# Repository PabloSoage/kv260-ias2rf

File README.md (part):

# KV260-IAS2RF: an RF front-end carrier for the AMD Kria KV260

**Status (20 November 2026, Rev08.1): schematic and layout complete, on 8 layers. The board is fully routed, with zero
DRC errors and zero schematic-parity problems. It has not been fabricated, and no hardware has
been validated.** The hardware, dual-FPGA Vivado gateware, Enclosure v2 cooling, and full-system co-simulation are complete ([Status](#status)).

> **Current `main` Hardware & Gateware Baseline:** **8-layer `JLC08161H-2116C`** RF front-end adapter PCB with dedicated-pin **1000BASE-T Ethernet (`U1201 RTL8211FSI`) + dual-lane `IAS1` (`~2.94 Gb/s` aggregate)**, failover in the dual-FPGA Vivado 2026.1 gateware ([docs/FPGA_GATEWARE.md](docs/FPGA_GATEWARE.md)), `5 V` header `J1002` for filtered Enclosure v2 active cooling ([ENCLOSURE.md](docs/ENCLOSURE.md)), and `0` KiCad DRC / parity errors. Historical design evolution from initial drafts is archived in [docs/history/README.md](docs/history/README.md) and tagged `rev01` to `rev08.1`.

**Explore it in 3-D:** [pablosoage.github.io/kv260-ias2rf](https://pablosoage.github.io/kv260-ias2rf/). Turn the board, the KV260 and the enclosure, open the case, hover a part to see what it is and what it does, and look at the board layer by layer.

An adapter board for the **AMD Kria KV260 Vision AI Starter Kit**. It plugs into the KV260's IAS1
camera connector and carries the converters, a common clock and a front-end FPGA. It serves two
signal chains:

- **Software-defined radio**: HF to 30 MHz directly; FM, airband, VHF/UHF amateur bands, PMR446 and ADS-B
  through the on-board VHF/UHF front end on its own SMA, 30 MHz to 3 GHz ([RX_VU_SPEC](docs/RX_VU_SPEC.md)).
  Receive, and transmit on the bands a licence covers.
- **Radar at 10.5 GHz**: the IF of the X-band chain from the open
  [AERIS-10 / PLFM_RADAR](https://github.com/NawfalMotii79/PLFM_RADAR) project, with ADAR1000
  beamforming. The 10.5 GHz chain itself is reused from AERIS-10, not redesigned here. The board
  is sized for 8 ADAR1000s (32 channels), so it covers both the Nexus variant (4 chips) and the
  Extended one (8 chips).

> ### The finding that shapes the whole project
>
> The **IAS0 (J7) connector on the KV260 does not reach the programmable logic**: its MIPI lanes
> run into an AP1302 ISP soldered on the carrier card. Only **IAS1 (J8)** is wired straight to
> the SOM. On top of that, **the KV260 has no 40-pin Raspberry Pi header** (J9 is a 15-pin
> camera connector), and **the GTH transceivers are not exposed**.
>
> The real I/O budget between a KV260 and an external board is **8 differential pairs and about
> 14 single-ended signals**. That is why the board has its own FPGA. The evidence and sources are
> in [docs/BLOCKERS_AND_RISKS.md](docs/BLOCKERS_AND_RISKS.md).

---

## The board at a glance

| | |
|---|---|
| Size | 119 × 132 mm, 140 × 132 with the RJ45's tab. It mounts on the KV260's IAS connectors and corner holes and overhangs to one side ([INTERFACE_SPEC §5.3](docs/INTERFACE_SPEC.md)) |
| Stackup | 8 layers, JLCPCB `JLC08161H-2116C`: `L1 SIG – L2 GND – L3 SIG – L4 PWR (split) – L5 GND – L6 SIG – L7 GND – L8 SIG` ([LAYOUT §3](docs/LAYOUT.md)) |
| Parts | 785 fitted, the same count as the BOM and the placement file: 620 on the top face and 165 on the bottom (the Hirose connectors, the LVDS terminations and VCCINT caps under the FPGA, the switches' bias parts, the input protection) |
| Front-end FPGA | Xilinx XC7A50T-2FTG256I (the same part as AERIS-10) with a 128 Mb QSPI flash, plus JTAG |
| Radar ADC | AD9484, 8 bit: 400 MSPS with the 400 MHz master clock (radar), 500 MSPS with the 500 MHz one (the D2 path), driven by two cascaded AD8352s |
| SDR ADC | AD9253, 14 bit, two channels at 62.5 MSPS (one LVDS lane each) |
| Radar DAC | AD9708, with reconstruction filter and balun |
| SDR DAC | AD9767, dual 14 bit, two output chains |
| Clock | Si549 programmable XO (400 or 500 MHz, GPS-disciplinable) into an ADCLK948 LVPECL fan-out |
| RF routing | Four M3SWA2-34DR+ SPDT switches and ten edge SMAs, plus two clock SMAs and the VHF/UHF antenna SMA `J961` on the back wall: thirteen in all. The HF ports J951 (receive, through an on-board 30 MHz 7th-order elliptic anti-alias filter) and J952 (transmit) have no switch in their path ([SIGNAL_INTEGRITY §9.9](docs/SIGNAL_INTEGRITY.md)) |
| Link to the Kria | IAS1 (Hirose BM20B), five LVDS pairs at up to 1 Gb/s each, AC-coupled; the Pmod J2 for control |
| Ethernet | Gigabit RJ45 through an RTL8211FSI SGMII PHY on its own FPGA pins, so it runs alongside IAS1 ([CONTROL_SPEC §8](docs/CONTROL_SPEC.md)) |
| To AERIS-10 | 2×20 IDC ribbon for eight ADAR1000s |
| Power | 12 V single power entry (`J1001` via `L1004` to adapter + `U1010`/`J1004` 3.0 A output to KV260 `J12`); buck and LDO tree for 5 V, 3.3 V, 2.5 V, 1.8 V and 1.0 V, plus -3.3 V for the switches ([POWER_SPEC §1.4](docs/POWER_SPEC.md), [BOARD_MANUAL §6](docs/BOARD_MANUAL.md#6-powering-the-kv260-together-with-the-board)). In a vehicle, the [PSU board](docs/PSU_SPEC.md) feeds both boards from the battery |

```mermaid
flowchart LR
  KV260["Kria KV260<br/>(K26 SOM)"] <-- "IAS1: 5 LVDS pairs<br/>Pmod: control" --> FPGA["XC7A50T<br/>front-end FPGA"]
  FPGA <-- LVDS --> ADCR["AD9484<br/>radar ADC"]
  FPGA <-- LVDS --> ADCS["AD9253<br/>SDR ADC"]
  FPGA --> DACR["AD9708<br/>radar DAC"]
  FPGA --> DACS["AD9767<br/>SDR DAC"]
  CLK["Si549 + ADCLK948<br/>clock"] --> ADCR & ADCS & DACR & DACS & FPGA
  ADCR & ADCS & DACR & DACS <--> RF["RF switches<br/>10 SMAs"]
  FPGA <-- "IDC ribbon" --> AERIS["AERIS-10<br/>8 × ADAR1000"]
  RF <--> AERIS
```

| Top | Bottom |
|---|---|
|  |  |

The renders come from KiCad. The shield frames' walls show only their pads; the debug USB-C `J1501` has a model
drawn from its maker's drawing, since no library has one ([3D_MODELS](docs/3D_MODELS.md)).

---

<!-- board-manual:start -->
## Board manual

Every connector, LED, switch and chip, numbered as in the drawing; the bottom side, the switches, the chips, troubleshooting and typical uses are in [docs/BOARD_MANUAL.md](docs/BOARD_MANUAL.md). Generated with the tables from the board file by `_work/manual/board_manual.py`.

| No. | Ref | Side | Name | What it is for |
|---|---|---|---|---|
| 1 | `J101` | bottom | BM20B(0.8)-34DP | IAS1 to the KV260 (its `J8`), underneath: five LVDS pairs at up to 1 Gb/s each (three data lanes, two clocks), the housekeeping I2C (temperature sensor, ID EEPROM) and the FPGA's interrupt. The board's only data link to the Kria |
| 2 | `J102` | bottom | BM20B(0.8)-34DP | IAS0 to the KV260 (its `J7`), underneath. Every pin is passed through to `J103`; the board uses none |
| 3 | `J103` | top | BM20B(0.8)-34DS-0.4V(51) | IAS0 pass-through receptacle on the tongue's top face, pin for pin with `J102`: an IAS camera module plugs in here as it would on the carrier |
| 4 | `J401` | top | CLK_REF_IN | Reference clock input (SMA) to the ADCLK948, 0.4-3.4 V p-p differential range, 50 ohm on chip. Leave open to run from the on-board Si549 |
| 5 | `J402` | top | CLK_OUT | Clock output (SMA), ADCLK948 Q3, LVPECL: to share the master clock with an instrument |
| 6 | `J911` | top | SDR_RX_A | SDR receive A (SMA): through SW1's default throw to the AD9253 channel A. Full scale about -2.4 dBm; DC-blocked |
| 7 | `J912` | top | AERIS_IF_A | Radar IF into the 14-bit AD9253 (SMA), through SW1's second throw |
| 8 | `J921` | top | AERIS_IF | Radar IF from AERIS-10 (SMA): through SW2's default throw to the AD9484 (400 or 500 MSPS with the master clock). Full scale about -17.6 dBm |
| 9 | `J922` | top | SDR_RX_WB | Wideband SDR receive (SMA), SW2's second throw. Not connected as built: `C926` is not fitted and the VHF/UHF front end takes the throw (`C927`); swap the two 0402s to use this port |
| 10 | `J931` | top | SDR_TX_A | SDR transmit A (SMA): AD9767 DAC1 through SW3's default throw, 10 mA full scale |
| 11 | `J932` | top | AERIS_TX_A | Radar chirp from the 14-bit AD9767 DAC1 (SMA), SW3's second throw |
| 12 | `J941` | top | AERIS_TX | Radar chirp to AERIS-10 (SMA): the AD9708 through SW4's default throw, 20 mA full scale into a 2:1 balun |
| 13 | `J942` | top | SDR_TX_WB | Wideband SDR transmit from the AD9708 (SMA), SW4's second throw |
| 14 | `J951` | top | SDR_RX_C | HF receive (SMA), no switch: a 30 MHz 7th-order elliptic low-pass, then the AD9253 channel B. Full scale about -3.0 dBm. The default HF input |
| 15 | `J952` | top | SDR_TX_C | HF transmit (SMA), no switch: AD9767 DAC2. The default HF output |
| 16 | `J961` | top | VU_ANT | VHF/UHF antenna (SMA, back wall): the Rev08 front end, direct 30-170 MHz and converted from 300 MHz to 3 GHz (170-300 MHz not covered: the converter's 300 MHz high-pass, AUDIT_Rev08 R1), into the AD9484 through SW2. Bias tee for an active antenna (off at power-up, 5 V or 3.3 V by `JP1301`, 125 mA limit; prefer 3.3 V where the antenna accepts it). Full scale -52 dBm at maximum gain, up to about +2 dBm with the attenuator and the LNA bypassed. No limiter: keep it away from a transmitter on the same vehicle (+25 dBm destroys the LNA) |
| 17 | `J1001` | top | 12V IN | 12 V input, barrel jack (CUI PJ-102AH, 5 A). Single power entry for both boards (`L1004` on both lines): feeds the adapter (11.7 W typical, 13.4 W / 1.12 A worst; `F1001` 2 A PTC, 18.3 V OVP) and the KV260 via `U1010`/`J1004` (3.0 A / 3.19 A max limit; 1.89 A typical, 4.12 A rated, 4.31 A worst combined). See POWER_SPEC section 1.4 and section 6 |
| 18 | `J1002` | top | FAN 5V | Enclosure fan, JST PH 2-pin: pin 1 +5 V (0.5 A PTC `F1002`), pin 2 GND |
| 19 | `J1004` | top | B2PS-VH | 12 V output to the KV260's `J12` (JST VH 2-pin right-angle, 10 A: pin 1 `+12V_KV`, pin 2 `GND`): protected by `U1010` (8.0 V UVLO, 14.4 V OVP, 3.0 A limit via `R1043` 6.04 kohm, -60 V reverse); see section 6 |
| 20 | `J1101` | top | JTAG 2x7 2mm | Xilinx JTAG for the XC7A50T and its flash (Platform Cable or any 2 mm 14-pin JTAG adapter) |
| 21 | `J1102` | top | Pmod | Pmod from the KV260's `J2` (cable): SPI to the FPGA's register file, beam strobe, PPS and the debug UART. Pin by pin below |
| 22 | `J1103` | top | AERIS ADAR | AERIS-10 beam-steering ribbon (2x20 IDC): the ADAR1000 SPI and its control lines |
| 23 | `J1201` | top | HR911130C | Gigabit Ethernet (RJ45, magnetics and LEDs inside), from the RTL8211FS over SGMII to the FPGA: the board standalone |
| 24 | `J1501` | top | TYPE-C-31-E-17 | Debug USB-C (vertical, on the tongue): the FPGA's console through a CH340X, 115,200 baud 8N1, powered from the cable. Lid off |
| 25 | `J1502` | top | FPC-1.0FX-15PWCR-H20 | GPS PPS and the vehicle CAN to the KV260's `J9` (Raspberry Pi camera connector) by a 100 mm 15-way 1 mm FFC, either cable type: the pulse reaches `J9` pin 12, a PL pin (`kria_pps`); CAN TX leaves on `J9` pin 6 and RX comes back on pin 8 (PS `CAN1`, R5F core 1) |
| 26 | `J1503` | top | BM06B-SRSS-TB | GPS receiver and vehicle CAN, JST-SH 6-pin, vertical, the plug from above: 1 GND, 2 CANL, 3 CANH, 4 GND, 5 PPS in (3.3 V), 6 +3.3 V out (0.2 A PTC) (no termination: it taps the car's bus) |

| No. | LED | Meaning when lit |
|---|---|---|
| 30 | `D1501` CFG green | FPGA configured and the clock sequencer finished |
| 30 | `D1502` CLK yellow | Master clock mode: on 500 MHz, off 400 MHz |
| 30 | `D1503` LINK green | IAS1 link to the Kria trained |
| 30 | `D1504` ADCR red | The radar ADC (AD9484) clipped since the last read (sticky) |
| 30 | `D1505` ADCS red | The SDR ADC (AD9253) clipped since the last read (sticky) |
| 30 | `D1506` LO green | The RFFC5072 synthesiser is locked |
| 30 | `D1507` TX red | A DAC is driving an SMA |
| 30 | `D1508` ERR red | Any sticky error: CRC, FIFO overflow, I2C no-acknowledge, over-temperature |
| 30 | `D1509` HB blue | Heartbeat: flickers with every line the FPGA prints on the debug UART, once a second |
| 31 | `D1520` +12V green | +12V present (after the input protection) |
| 31 | `D1521` +5V0 green | +5V0 present |
| 31 | `D1522` +3V3_D green | +3V3_D present |
| 31 | `D1523` +1V8_D green | +1V8_D present (switched from +3V3_D by `Q1520`) |
| 31 | `D1524` +1V0 green | +1V0 (FPGA core) present (switched from +3V3_D by `Q1521`) |
| 32 | `D1101` green | DONE: the FPGA has loaded a bitstream |
<!-- board-manual:end -->

---

## Schematics and layout

The PDFs and the high-resolution files are not in the repository: they are assets of the [`rev08.1` release](https://github.com/PabloSoage/kv260-ias2rf/releases/tag/rev08.1) (each older tag has its own), and the books open in the [online reader](https://pablosoage.github.io/kv260-ias2rf/pdf.html?file=docs/KV260-IAS2RF_Documentation.pdf).

- **[Schematic, all 12 sheets including full wired overview (PDF)](https://github.com/PabloSoage/kv260-ias2rf/releases/download/rev08.1/KV260-IAS2RF_schematic.pdf)** · [High-res SVGs & 4K PNGs](https://github.com/PabloSoage/kv260-ias2rf/releases/download/rev08.1/KV260-IAS2RF_highres.zip) ([index](docs/img/highres/README.md#1-schematics-sch))
- **[Layout, all 8 copper layers + combined + transparent tracks (PDF)](https://github.com/PabloSoage/kv260-ias2rf/releases/download/rev08.1/KV260-IAS2RF_layout.pdf)** · [Per-layer SVGs & 4K PNGs](https://github.com/PabloSoage/kv260-ias2rf/releases/download/rev08.1/KV260-IAS2RF_highres.zip) ([index](docs/img/highres/README.md#2-8-layer-pcb-layout-layout))
- **[Complete Project Documentation Book (PDF)](https://github.com/PabloSoage/kv260-ias2rf/releases/download/rev08.1/KV260-IAS2RF_Documentation.pdf)**, and the same book lighter, with the normal renders instead of the 4K ones: [Lite PDF](https://github.com/PabloSoage/kv260-ias2rf/releases/download/rev08.1/KV260-IAS2RF_Documentation-Lite.pdf) (both reproducible locally via [`export_documentation.py`](export_documentation.py), `--lite` for the second)
- KiCad 10 sources: [`KV260-IAS2RF.kicad_pro`](KV260-IAS2RF.kicad_pro), the root
  schematic and [`sheets/`](sheets/) (twelve hierarchical sheets), the 8-layer board
  [`KV260-IAS2RF.kicad_pcb`](KV260-IAS2RF.kicad_pcb), and custom libraries in
  [`symbols/`](symbols/) and [`footprints/`](footprints/). Every title block carries the revision, Rev08.1; the original Allied Vision Altium project the board started from stays in `PCB/` under its own name ([docs/history/README.md](docs/history/README.md)).

| Sheet | Contents | Specification |
|---|---|---|
| [Full Circuit](docs/img/sch/ROOT.png) | Complete wired schematic overview & hierarchy (`FULL_CIRCUIT` + `ROOT`) | [ARCHITECTURE](ARCHITECTURE.md) |
| [IAS_LINK](docs/img/sch/IAS_LINK.png) | The Hirose connectors, AC coupling and terminations of the link | [IAS_LINK_SPEC](docs/IAS_LINK_SPEC.md) |
| [CLOCK](docs/img/sch/CLOCK.png) | Si549, reference select and LVPECL fan-out | [CLOCK_SPEC](docs/CLOCK_SPEC.md) |
| [ADC_RADAR](docs/img/sch/ADC_RADAR.png) | AD9484 and its two AD8352 drivers | [ADC_RADAR_SPEC](docs/ADC_RADAR_SPEC.md) |
| [ADC_SDR](docs/img/sch/ADC_SDR.png) | AD9253, two channels | [ADC_SDR_SPEC](docs/ADC_SDR_SPEC.md) |
| [DAC_RADAR](docs/img/sch/DAC_RADAR.png) | AD9708, filter and balun | [DAC_RADAR_SPEC](docs/DAC_RADAR_SPEC.md) |
| [DAC_SDR](docs/img/sch/DAC_SDR.png) | AD9767 in interleaved mode, two output chains | [DAC_SDR_SPEC](docs/DAC_SDR_SPEC.md) |
| [ROUTING](docs/img/sch/ROUTING.png) | Four RF switches and the SMAs | [ROUTING_SPEC](docs/ROUTING_SPEC.md) |
| [CONTROL](docs/img/sch/CONTROL.png) | The front-end FPGA: banks, configuration, Pmod, AERIS ribbon, housekeeping | [CONTROL_SPEC](docs/CONTROL_SPEC.md) |
| [POWER](docs/img/sch/POWER.png) | The power tree | [POWER_SPEC](docs/POWER_SPEC.md) |
| [RX_VU](docs/img/sch/RX_VU.png) | VHF/UHF front end (`J961`), LNA, preselectors, RFFC5072 and IF chain | [RX_VU_SPEC](docs/RX_VU_SPEC.md) |
| [STATUS](docs/img/sch/STATUS.png) | Status LEDs, TCA6416A expanders, debug USB-C UART, GPS PPS and vehicle CAN | [BOARD_MANUAL](docs/BOARD_MANUAL.md#3-leds) |
| [KVPWR](docs/img/sch/KVPWR.png) | KV260 single-entry power feed: `J1004`, `L1004` CMC, `U1010` 3.0 A eFuse | [POWER_SPEC](docs/POWER_SPEC.md#14-single-power-entry-and-the-kv260-output-rev08-19-nov) |

> *High-resolution vector PDF (`sch/FULL_CIRCUIT.pdf` in the [high-res archive](https://github.com/PabloSoage/kv260-ias2rf/releases/download/rev08.1/KV260-IAS2RF_highres.zip)) and 4K schematic PNGs are indexed in [docs/img/highres/README.md](docs/img/highres/README.md).*

---

## Status

| Check | Result |
|---|---|
| ERC | 0 errors; 7 warnings, all explained: configuration and XADC pins tied to power on purpose ([CONTROL_SPEC §5](docs/CONTROL_SPEC.md)) |
| DRC, zones refilled | **0 errors, 0 unrouted connections, 0 schematic-parity problems** on the 8-layer `JLC08161H-2116C` board (`local/kvpwr`, 785 BOM parts; checked by `make_fab.py`) |
| Signal and power integrity | Full-wave openEMS + ngspice verification ([SIGNAL_INTEGRITY.md](docs/SIGNAL_INTEGRITY.md)): SMA launch `S11 = -30.9 dB` at 1 GHz (`-13.7 dB` at 3 GHz) with ESD diode, LVDS eyes within `1–26 mV` of ideal except `LINK_RX_D0` (`-52 mV`), worst intra-pair skew `9 ps`, `VCCINT` impedance `41 / 63 mΩ` (`target 120 mΩ`), ESD protection on every SMA, Pmod and JTAG, GND via within `3 mm` of all `89` LVDS layer changes |
| Planes | L2, L5, and L7 carry solid ground; L4 carries split power islands (`_work/layout/planechk.py`) |
| Dual-FPGA gateware | Both designs place, route and meet timing in Vivado 2026.1; utilisation and slack in the [FPGA figures](#fpga-figures) table, generated from the Vivado reports. They pass the end-to-end XSim suite (`tb_system`, `S1..S6`) and the G-8 simulations ([FPGA_GATEWARE.md](docs/FPGA_GATEWARE.md)) |
| Final RF review (15 Nov) | Five limits found ([SIGNAL_INTEGRITY §9.8](docs/SIGNAL_INTEGRITY.md)) and addressed ([§9.9](docs/SIGNAL_INTEGRITY.md)): a 30 MHz 7th-order anti-alias filter on the HF input J951 (≥ 60 dB from 50 MHz); the switch-free J951/J952 as the default HF ports; DAC clocks from `CLK_FPGA` ÷ 4 without an MMCM (clock uncertainty `0.165 → 0.035 ns`); no transmit copper within 1.5 mm of any receive line; the enclosure's honest rating below. Still to measure on the first board: TX→RX isolation, the RF switches at 1–5 MHz, the filter above 700 MHz, switcher spurs |
| Rev08 front end and diagnostics (16–17 Nov) | VHF/UHF receive on `J961`, 30 MHz to 3 GHz: noise figure 2.0 dB and full scale −52 dBm at maximum gain in the direct VHF path, FM-reject ≥ 40 dB with real tolerances; `J961` launch `S11 ≤ −18.1 dB` to 1.1 GHz with its ESD diode and bias tee; no front-end copper within 1.5 mm of either ADC input or the clock tree ([REV08_PLAN §5.5, §11.7](docs/REV08_PLAN.md), [SIGNAL_INTEGRITY §9.10](docs/SIGNAL_INTEGRITY.md)). 14 status and rail LEDs, a USB-C debug console, the IAS0 camera pass-through, and the [board manual](docs/BOARD_MANUAL.md) |
| Rev08.1 power and the PSU board (19 Nov) | One supply and one ground for both boards (sheet `KVPWR`, [POWER_SPEC §1.4](docs/POWER_SPEC.md), [AUDIT_Rev08 §6](docs/AUDIT_Rev08.md)); the [PSU board](docs/PSU_SPEC.md) feeds both from the battery through ISO 16750-2 Load Dump A/B, jump start and cranking Levels I, II and IV; its audit, ERC 0 and DRC 0 / 0 ([PSU_SPEC §10](docs/PSU_SPEC.md)) |
| Mechanical fit | Registered on AMD's 3D model of the KV260: mounting holes land within `5 µm` ([INTERFACE_SPEC §5.3](docs/INTERFACE_SPEC.md)) |

**Design & verification highlights** ([docs/LAYOUT.md](docs/LAYOUT.md), [docs/SIGNAL_INTEGRITY.md](docs/SIGNAL_INTEGRITY.md)):

1. **Power & analog isolation.** Supply trunks widened (`865 mm` at `>= 0.5 mm`); `+1V8_A` trimmed to `1.85 V`; DAC1/DAC2 filters colocated under their baluns (`T801`/`T802`), dropping balun common mode by `9–21 dB` (DAC2) and `1–6 dB` (DAC1); `FB401` upgraded to a `2 A / <= 0.1 Ω` bead (`48 mV` drop max, `0.1–0.4 mVpp` ripple on the clock tree).
2. **Differential pairs & LVDS routing.** Nine of 19 data/link pairs plus `CLK_ADCS` and `CLK_FPGA` run coupled `100 Ω` end-to-end on L1/L3/L6; the remaining pairs use `50 Ω` legs matched to `<= 9 ps` worst-case intra-pair skew with on-pad `100 Ω` terminations.
3. **ADCR data to DCO skew (`-90 to +5 ps`).** `ADCR_DCO` legs are swapped cleanly at the Artix-7 BGA (`N14 = DCO_N`, `P14 = DCO_P`); `adc_capture.v` compensates with `ISERDESE2` inversion + per-bit `IDELAYE2` calibration.
4. **8-layer `JLC08161H-2116C` fabrication stack.** Controlled impedances verified against JLCPCB's solver ([FABRICATION.md](docs/FABRICATION.md)); 5 bare boards quoted at `$287.96` (`140 × 132 mm` with Ethernet tab).
5. **Kria IAS1 I/O standard.** `DIFF_SSTL12` with `RTT_48` on-die split termination (`~96 Ω` to `0.6 V`) and `RDRV_60_60` driver ([INTERFACE_SPEC §6.3](docs/INTERFACE_SPEC.md)); `2 Gb/s` uplink (`2` pairs) + `1 Gb/s` downlink (`1` pair), `1.25 Gb/s` per lane silicon headroom.
6. **3-D full-wave EM, RF cascade & thermal envelope.** openEMS 3-D sub-models cover L1–L6 vias (`S11 < -29 dB`), BGA escapes (`< -24 dB`), adjacent-pair NEXT (`1.9%`), and `J101` launch (`< -25 dB`). Receive cascades (`cascade.py`) give `NF = 26.8 dB` (radar) / `22 dB` (SDR). Enclosure v2 (`50 × 50 × 15 mm` filtered lid fan + `HS1`–`HS3` heatsinks) is rated for `56 °C` ambient with the stock KV260, whose commercial K26 is the limit (`Tj` `85 °C`), and `70 °C` with an industrial K26I SOM, unchanged by Rev08's front end and camera ([ENCLOSURE_V2_THERMAL.md §8](docs/ENCLOSURE_V2_THERMAL.md)).
7. **Dual-FPGA Vivado 2026.1 gateware & XSim verification.** Full RTL, constraints, Vivado post-route floorplans/schematics, and XSim end-to-end testbenches live in `fpga/` ([docs/FPGA_GATEWARE.md](docs/FPGA_GATEWARE.md)). *(Design evolution history is archived in [docs/history/README.md](docs/history/README.md).)*

**Estimated cost** ([docs/JLCPCB_QUOTE.md](docs/JLCPCB_QUOTE.md)): about **$2,443 for two assembled boards** and **$4,785 for five** (19 Nov, single power entry + RJ45 shield RC; parts + assembly + `JLC08161H-2116C` bare boards).

---

## Documentation

| Document | Contents |
|---|---|
| **[docs/BOARD_MANUAL.md](docs/BOARD_MANUAL.md)** | **Board manual.** Every connector, LED, switch, jumper, test point and chip, with drawings of both sides, the Pmod pin-out, troubleshooting by LED and typical uses |
| **[docs/PSU_SPEC.md](docs/PSU_SPEC.md)** | **PSU board.** The battery-to-both-boards supply (`psu/`): LTC4364 surge stopper and LM5177 buck-boost, its simulations (steady state, loop, ISO 7637-2 and 16750-2 events, thermal, conducted noise) and installation |
| [docs/PSU_ENCLOSURE.md](docs/PSU_ENCLOSURE.md) | The PSU board's printed enclosure: honeycomb tray and lid, coupled thermal model (vents or sealed, ASA or PETG-CF), CalculiX FEA and renders |
| **[docs/VEHICLE_PLATFORM.md](docs/VEHICLE_PLATFORM.md)** | **System view.** Complete vehicle platform: LiDAR, SDR, radar, OBD2 |
| [docs/FPGA_GATEWARE.md](docs/FPGA_GATEWARE.md) | **Dual-FPGA Gateware.** Artix-7 + Kria K26 RTL, Vivado 2026.1 utilization/timing/floorplans/schematics, CSR map, wideband SDR & AERIS-10 radar DSP, and XSim e2e simulation |
| [docs/HMI.md](docs/HMI.md) | **In-car HMI.** The ten touchscreen screens, a Slint application in Rust that runs on the KV260 (Linux KMS), a PC or a phone's browser, its data service and the PL's result streams behind it, and which job runs on the PL, the A53s, the R5F cores, the GPU and the VCU |
| [docs/INTEGRATIONS.md](docs/INTEGRATIONS.md) | **Possible integrations.** USB GPS, a 77 GHz radar over CAN, engine live data through opendash (measured against an emulated ECU), a 3D LiDAR, their behaviour in fog, and `kria_bev_grid`, a fusion occupancy grid for the PL |
| [KV260-IAS2RF_Documentation.pdf](https://github.com/PabloSoage/kv260-ias2rf/releases/download/rev08.1/KV260-IAS2RF_Documentation.pdf) (release asset) | **Unified Offline Book.** Every document of the project in one PDF, with the vector Vivado floorplans, the 14-page schematic (12 sheets), the 10-page 8-layer layout, the PSU board's schematic and 5-page 4-layer layout, 4K renders, and simulations (generated via [`export_documentation.py`](export_documentation.py)) |
| [docs/SHOPPING_LIST.md](docs/SHOPPING_LIST.md) | Parts and checklist per stage, with indicative costs |
| [ARCHITECTURE.md](ARCHITECTURE.md) | Master system architecture and BOM |
| [docs/BLOCKERS_AND_RISKS.md](docs/BLOCKERS_AND_RISKS.md) | Engineering blockers closed, with evidence and sources, plus open risks |
| [docs/INTERFACE_SPEC.md](docs/INTERFACE_SPEC.md) | Pin map for J8 and the Pmod, mechanical envelope, adapter registration on KV260 |
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
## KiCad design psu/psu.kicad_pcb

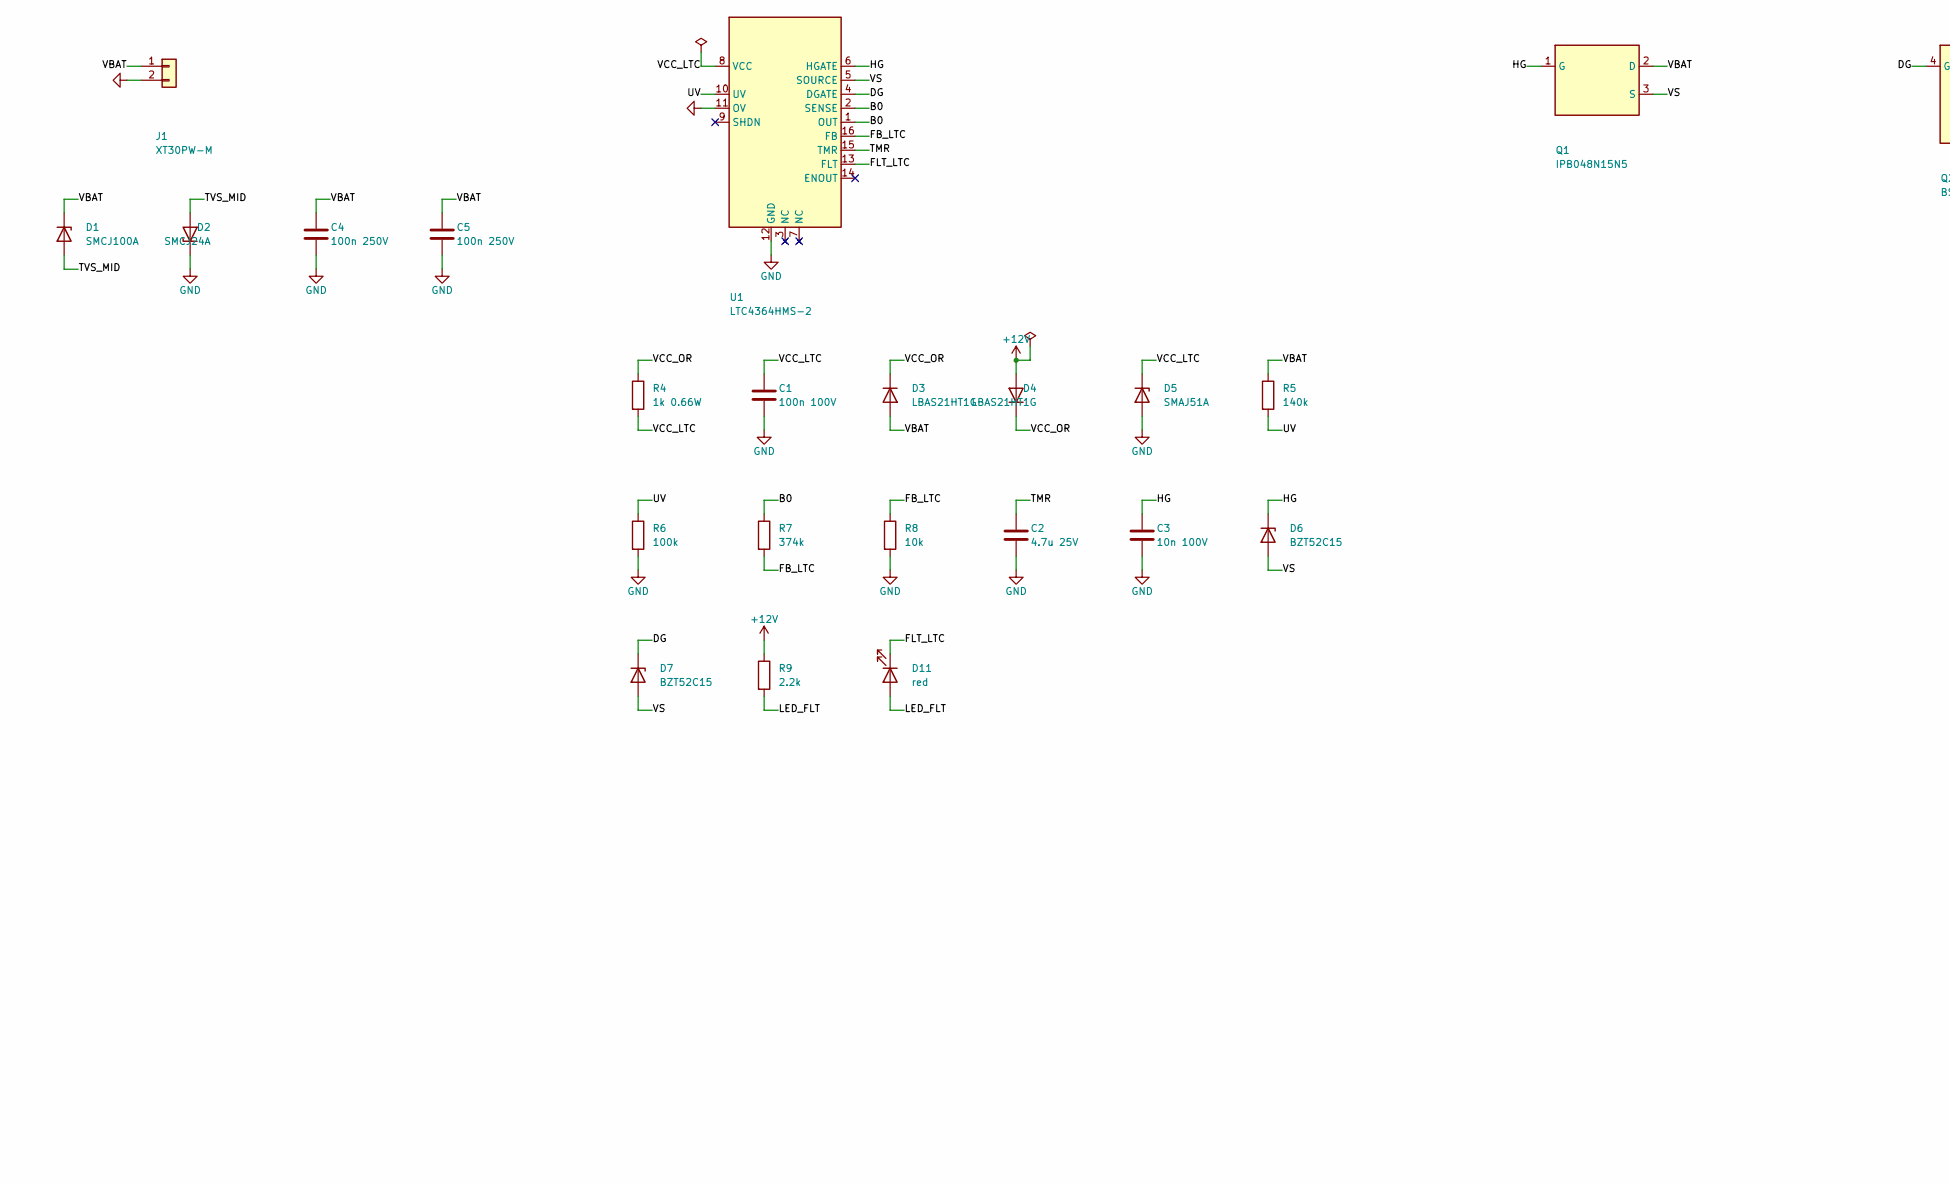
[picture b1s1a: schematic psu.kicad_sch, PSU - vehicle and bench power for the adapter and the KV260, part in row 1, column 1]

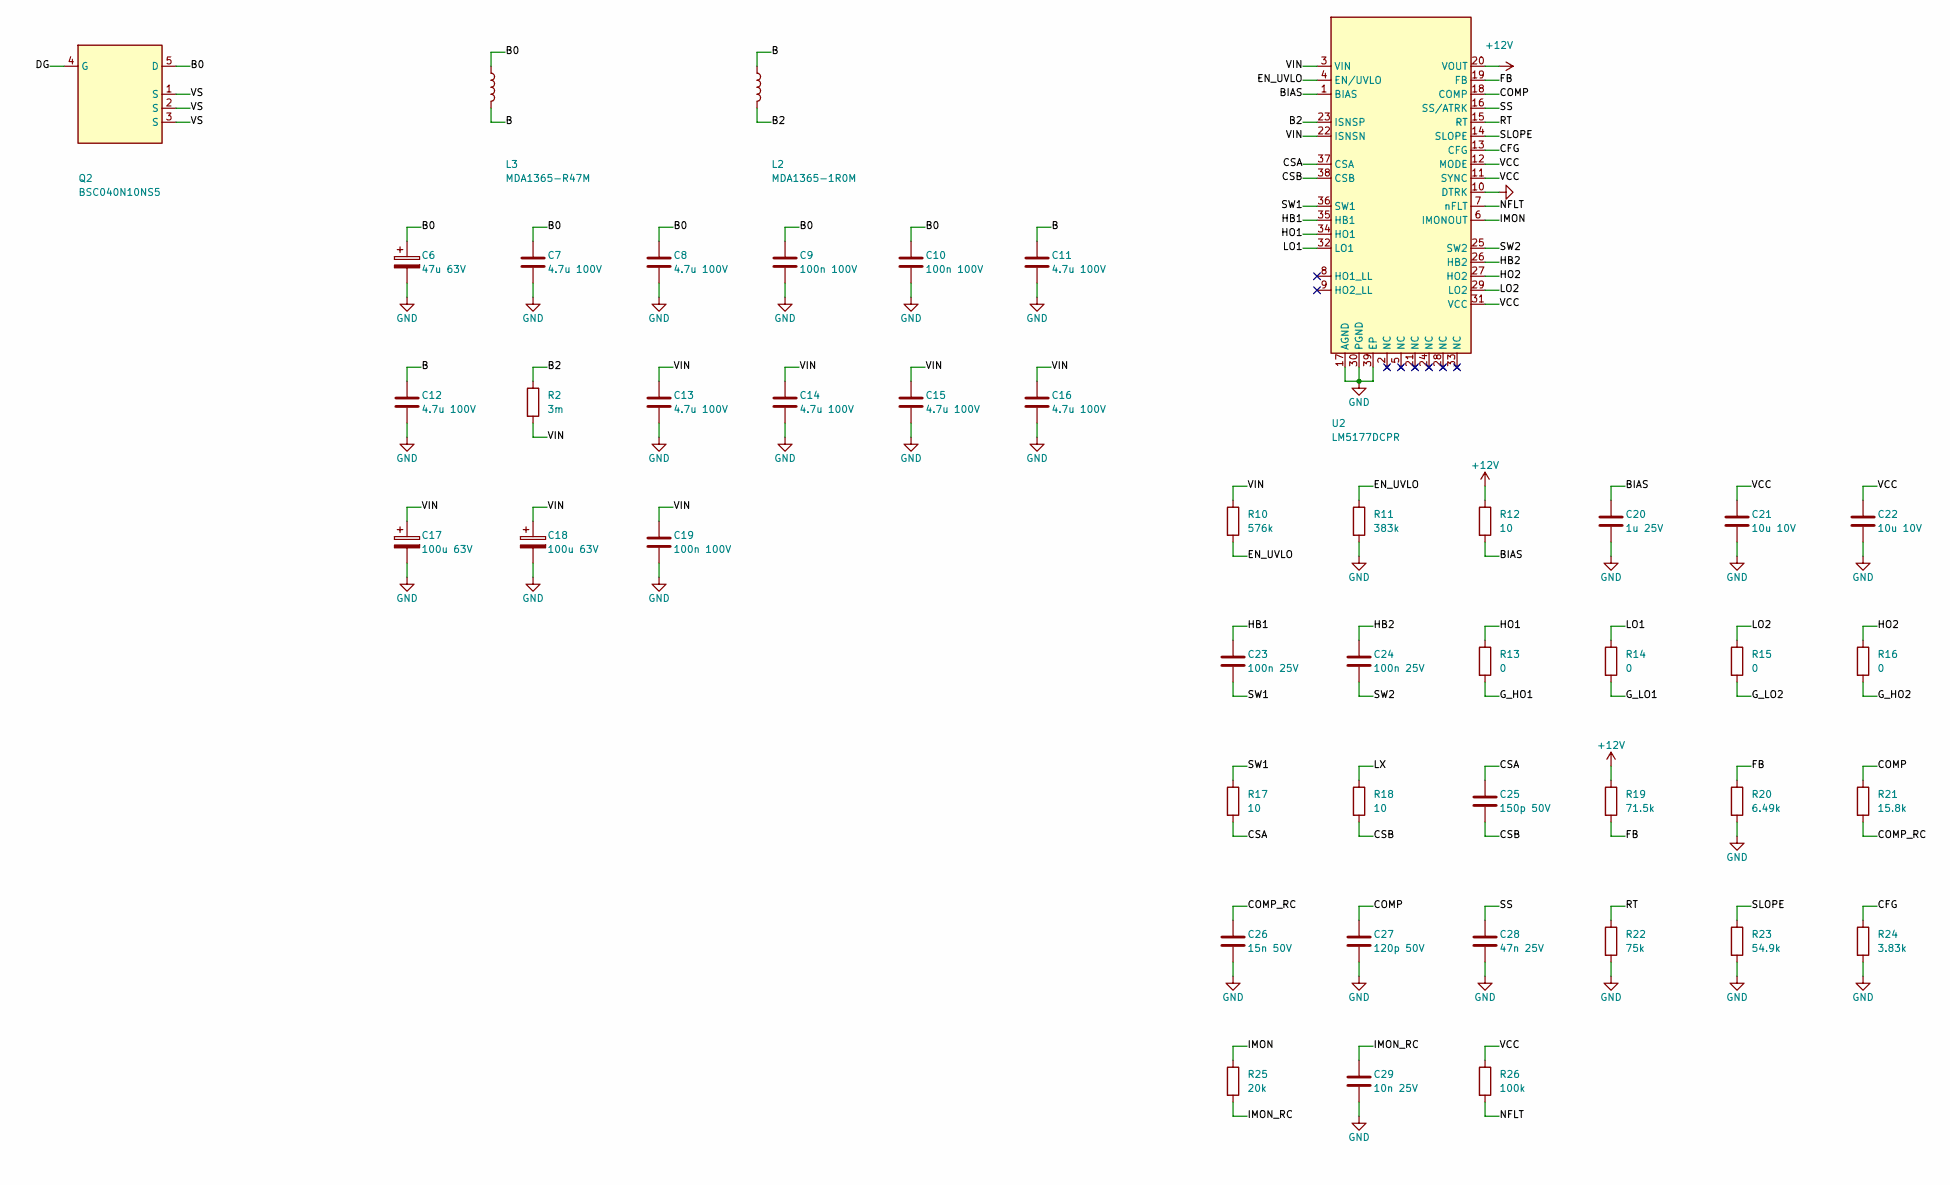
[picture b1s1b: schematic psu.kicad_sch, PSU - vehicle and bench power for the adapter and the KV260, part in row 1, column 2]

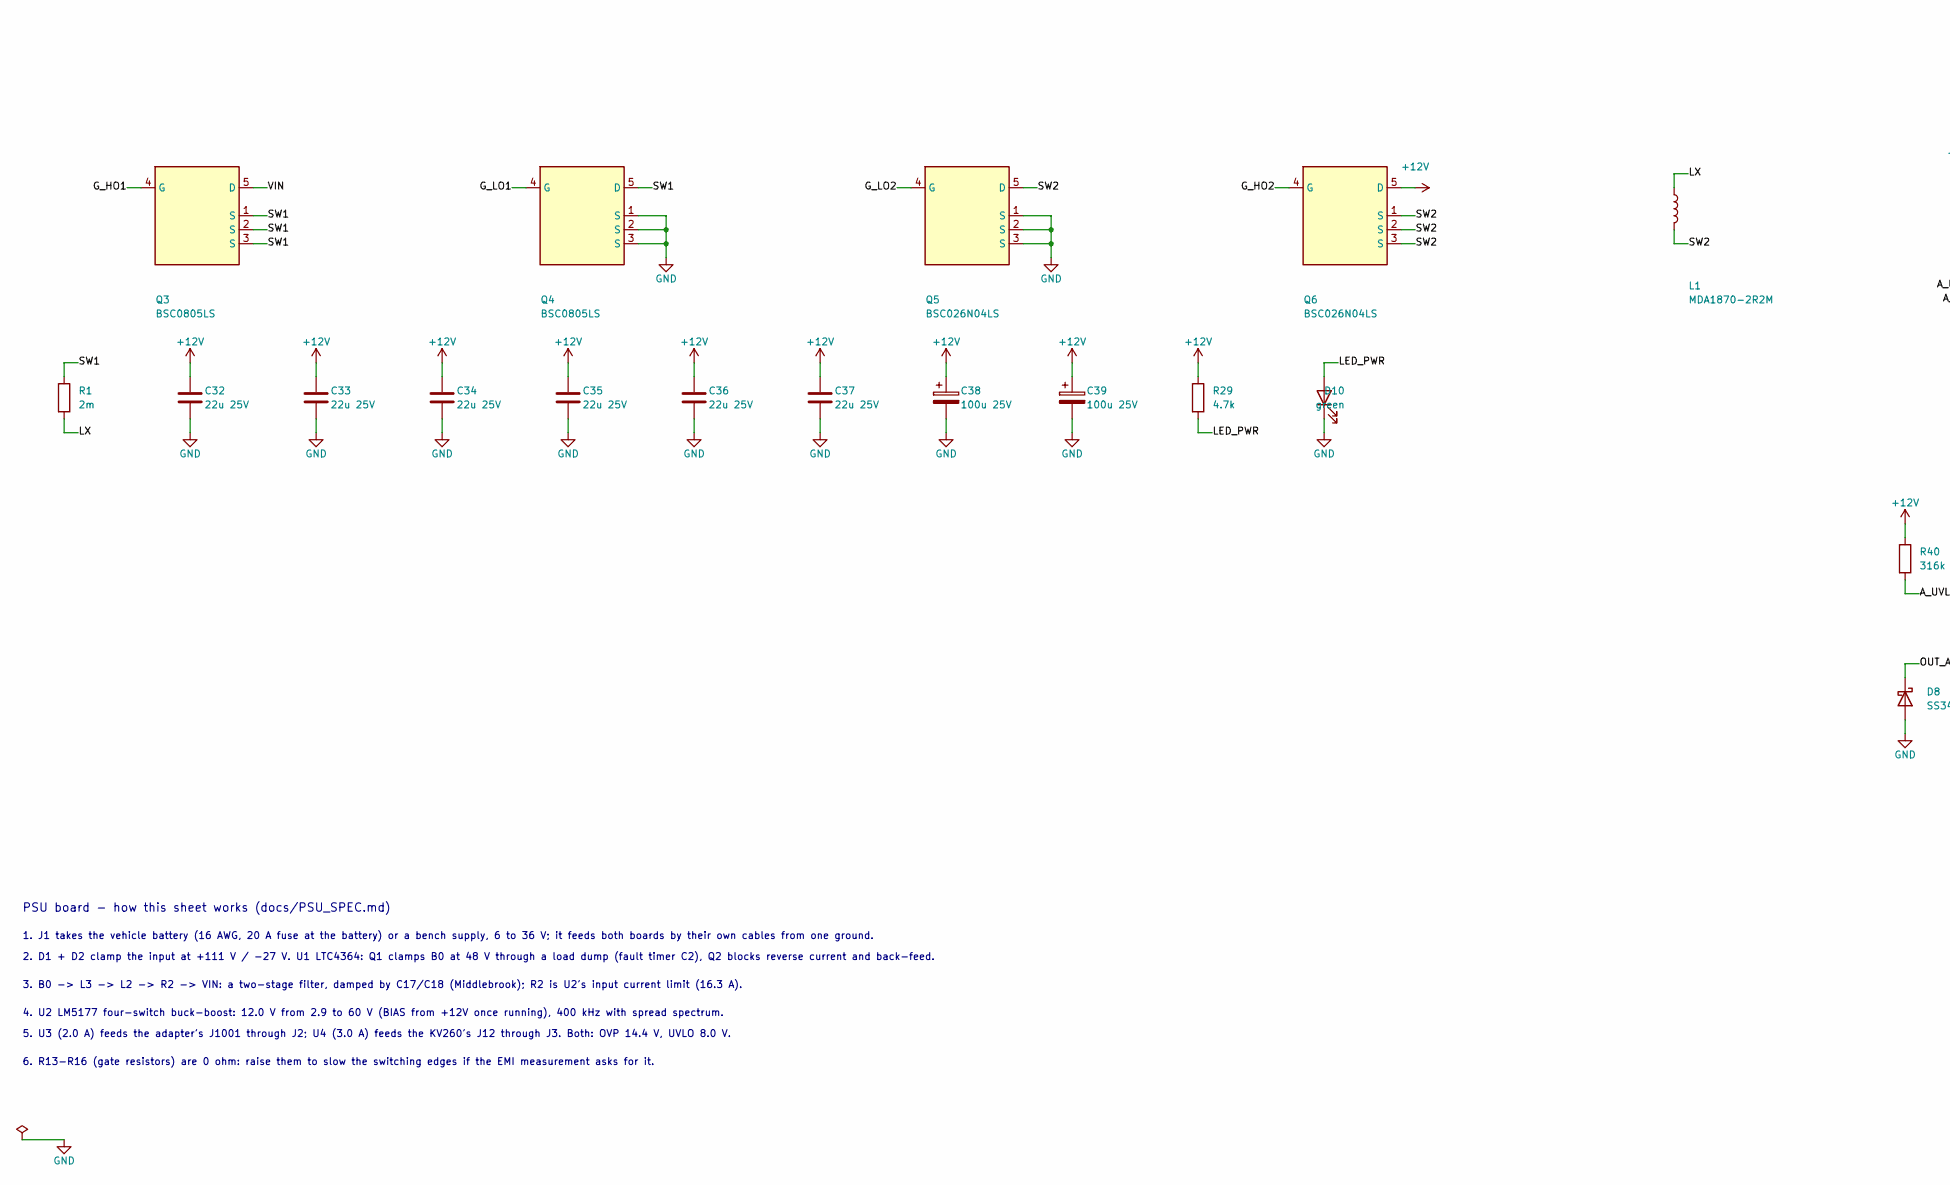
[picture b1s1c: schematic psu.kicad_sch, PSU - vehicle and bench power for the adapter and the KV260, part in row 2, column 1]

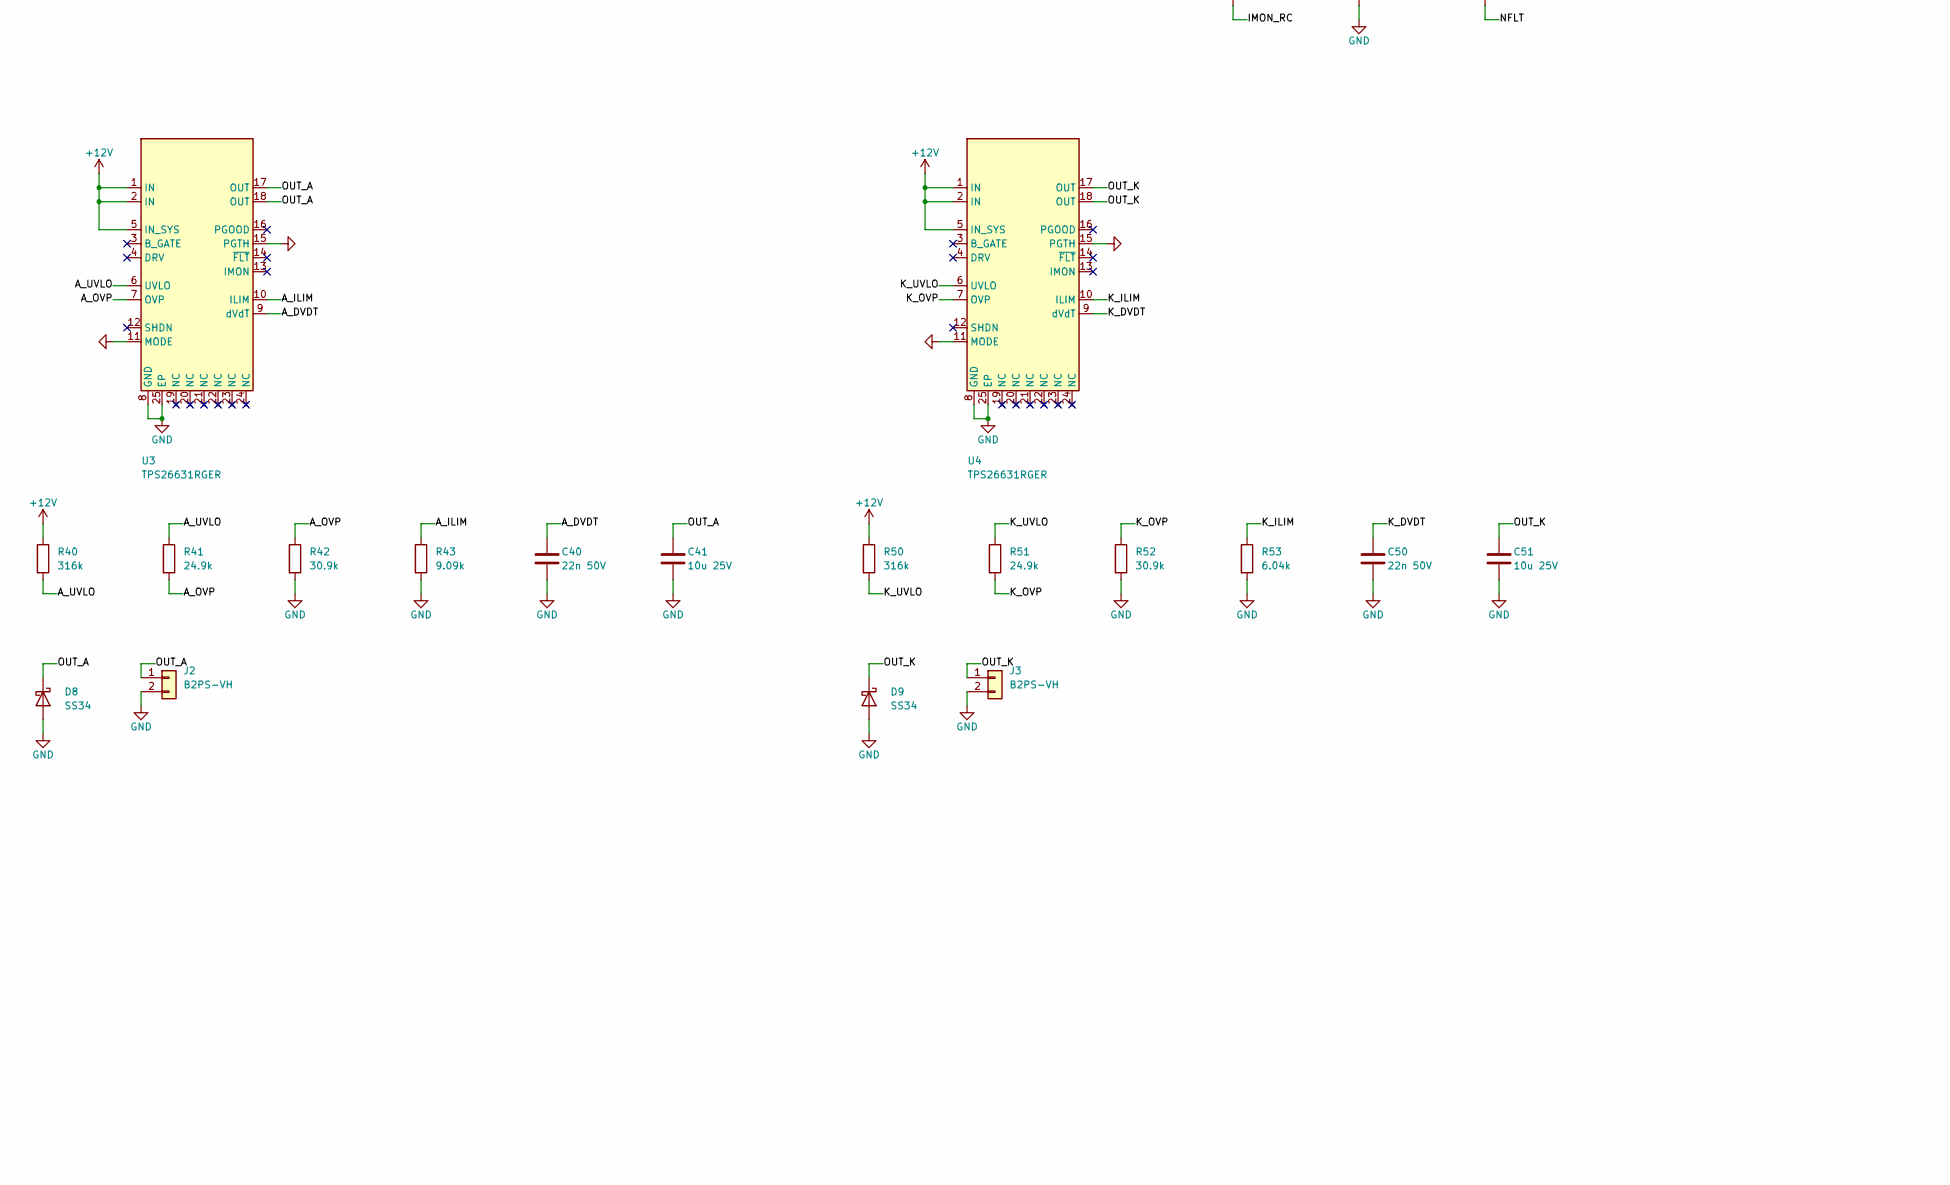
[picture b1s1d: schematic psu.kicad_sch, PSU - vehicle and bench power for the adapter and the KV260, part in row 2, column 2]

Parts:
C1: 100n 100V; C_0805_2012Metric
C2: 4.7u 25V; C_0805_2012Metric
C3: 10n 100V; C_0603_1608Metric
C4, C5: 100n 250V; C_1206_3216Metric
C6: 47u 63V; CP_Elec_8x10
C7, C8, C11, C12, C13, C14, C15, C16: 4.7u 100V; C_1210_3225Metric
C9, C10, C19: 100n 100V; C_0603_1608Metric
C17, C18: 100u 63V; CP_Elec_10x10
C20: 1u 25V; C_0603_1608Metric
C21, C22: 10u 10V; C_0805_2012Metric
C23, C24: 100n 25V; C_0603_1608Metric
C25: 150p 50V; C_0603_1608Metric
C26: 15n 50V; C_0603_1608Metric
C27: 120p 50V; C_0603_1608Metric
C28: 47n 25V; C_0603_1608Metric
C29: 10n 25V; C_0603_1608Metric
C32, C33, C34, C35, C36, C37: 22u 25V; C_1210_3225Metric
C38, C39: 100u 25V; CP_Elec_6.3x5.8
C40, C50: 22n 50V; C_0603_1608Metric
C41, C51: 10u 25V; C_1206_3216Metric
D1: SMCJ100A; D_SMC
D2: SMCJ24A; D_SMC
D3, D4: LBAS21HT1G; D_SOD-323
D5: SMAJ51A; D_SMA
D6, D7: BZT52C15; D_SOD-123
D8, D9: SS34; D_SMA
D10: green; LED_0603_1608Metric
D11: red; LED_0603_1608Metric
J1: XT30PW-M; AMASS_XT30PW-M_1x02_P2.50mm_Horizontal
J2, J3: B2PS-VH; JST_VH_B2PS-VH_1x02_P3.96mm_Horizontal
L1: MDA1870-2R2M; L_KOHER_MDA1870
L2: MDA1365-1R0M; L_KOHER_MDA1365
L3: MDA1365-R47M; L_KOHER_MDA1365
Q1: IPB048N15N5; TO-263-2
Q2: BSC040N10NS5; Infineon_PG-TDSON-8_6.15x5.15mm
Q3, Q4: BSC0805LS; Infineon_PG-TDSON-8_6.15x5.15mm
Q5, Q6: BSC026N04LS; Infineon_PG-TDSON-8_6.15x5.15mm
R1: 2m; R_2512_6332Metric
R2: 3m; R_2512_6332Metric
R4: 1k 0.66W; R_1206_3216Metric
R5: 140k; R_0603_1608Metric
R6, R26: 100k; R_0603_1608Metric
R7: 374k; R_0603_1608Metric
R8: 10k; R_0603_1608Metric
R9: 2.2k; R_0603_1608Metric
R10: 576k; R_0603_1608Metric
R11: 383k; R_0603_1608Metric
R12, R17, R18: 10; R_0603_1608Metric
R13, R14, R15, R16: 0; R_0603_1608Metric
R19: 71.5k; R_0603_1608Metric
R20: 6.49k; R_0603_1608Metric
R21: 15.8k; R_0603_1608Metric
R22: 75k; R_0603_1608Metric
R23: 54.9k; R_0603_1608Metric
R24: 3.83k; R_0603_1608Metric
R25: 20k; R_0603_1608Metric
R29: 4.7k; R_0603_1608Metric
R40, R50: 316k; R_0603_1608Metric
R41, R51: 24.9k; R_0603_1608Metric
R42, R52: 30.9k; R_0603_1608Metric
R43: 9.09k; R_0603_1608Metric
R53: 6.04k; R_0603_1608Metric
U1: LTC4364HMS-2; MSOP-16_3x4.039mm_P0.5mm
U2: LM5177DCPR; TI_DCP0038A_HTSSOP-38
U3, U4: TPS26631RGER; Texas_RGE0024H_VQFN-24-1EP_4x4mm_P0.5mm_EP2.7x2.7mm_Thermal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

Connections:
+12V: C32.1, C33.1, C34.1, C35.1, C36.1, C37.1, C38.1, C39.1, D4.2 (A), Q6.5 (D), R9.1, R12.1, R19.1, R29.1, R40.1, R50.1, U2.20 (VOUT), U3.1 (IN), U3.2 (IN), U3.5 (IN_SYS), U4.1 (IN), U4.2 (IN), U4.5 (IN_SYS)
/A_DVDT: C40.1, U3.9 (dVdT)
/A_ILIM: R43.1, U3.10 (ILIM)
/A_OVP: R41.2, R42.1, U3.7 (OVP)
/A_UVLO: R40.2, R41.1, U3.6 (UVLO)
/B: C11.1, C12.1, L2.1, L3.2
/B0: C6.1, C7.1, C8.1, C9.1, C10.1, L3.1, Q2.5 (D), R7.1, U1.1 (OUT), U1.2 (SENSE)
/B2: L2.2, R2.1, U2.23 (ISNSP)
/BIAS: C20.1, R12.2, U2.1 (BIAS)
/CFG: R24.1, U2.13 (CFG)
/COMP: C27.1, R21.1, U2.18 (COMP)
/COMP_RC: C26.1, R21.2
/CSA: C25.1, R17.2, U2.37 (CSA)
/CSB: C25.2, R18.2, U2.38 (CSB)
/DG: D7.1 (K), Q2.4 (G), U1.4 (DGATE)
/EN_UVLO: R10.2, R11.1, U2.4 (EN/UVLO)
/FB: R19.2, R20.1, U2.19 (FB)
/FB_LTC: R7.2, R8.1, U1.16 (FB)
/FLT_LTC: D11.1 (K), U1.13 (FLT)
/G_HO1: Q3.4 (G), R13.2
/G_HO2: Q6.4 (G), R16.2
/G_LO1: Q4.4 (G), R14.2
/G_LO2: Q5.4 (G), R15.2
/HB1: C23.1, U2.35 (HB1)
/HB2: C24.1, U2.26 (HB2)
/HG: C3.1, D6.1 (K), Q1.1 (G), U1.6 (HGATE)
/HO1: R13.1, U2.34 (HO1)
/HO2: R16.1, U2.27 (HO2)
/IMON: R25.1, U2.6 (IMONOUT)
/IMON_RC: C29.1, R25.2
/K_DVDT: C50.1, U4.9 (dVdT)
/K_ILIM: R53.1, U4.10 (ILIM)
/K_OVP: R51.2, R52.1, U4.7 (OVP)
/K_UVLO: R50.2, R51.1, U4.6 (UVLO)
/LED_FLT: D11.2 (A), R9.2
/LED_PWR: D10.2 (A), R29.2
/LO1: R14.1, U2.32 (LO1)
/LO2: R15.1, U2.29 (LO2)
/LX: L1.1, R1.2, R18.1
/NFLT: R26.2, U2.7 (nFLT)
/OUT_A: C41.1, D8.1 (K), J2.1, U3.17 (OUT), U3.18 (OUT)
/OUT_K: C51.1, D9.1 (K), J3.1, U4.17 (OUT), U4.18 (OUT)
/RT: R22.1, U2.15 (RT)
/SLOPE: R23.1, U2.14 (SLOPE)
/SS: C28.1, U2.16 (SS/ATRK)
/SW1: C23.2, Q3.1 (S), Q3.2 (S), Q3.3 (S), Q4.5 (D), R1.1, R17.1, U2.36 (SW1)
/SW2: C24.2, L1.2, Q5.5 (D), Q6.1 (S), Q6.2 (S), Q6.3 (S), U2.25 (SW2)
/TMR: C2.1, U1.15 (TMR)
/TVS_MID: D1.2 (A), D2.2 (A)
/UV: R5.2, R6.1, U1.10 (UV)
/VBAT: C4.1, C5.1, D1.1 (K), D3.2 (A), J1.1, Q1.2 (D), R5.1
/VCC: C21.1, C22.1, R26.1, U2.11 (SYNC), U2.12 (MODE), U2.31 (VCC)
/VCC_LTC: C1.1, D5.1 (K), R4.2, U1.8 (VCC)
/VCC_OR: D3.1 (K), D4.1 (K), R4.1
/VIN: C13.1, C14.1, C15.1, C16.1, C17.1, C18.1, C19.1, Q3.5 (D), R2.2, R10.1, U2.3 (VIN), U2.22 (ISNSN)
/VS: D6.2 (A), D7.2 (A), Q1.3 (S), Q2.1 (S), Q2.2 (S), Q2.3 (S), U1.5 (SOURCE)
GND: C1.2, C2.2, C3.2, C4.2, C5.2, C6.2, C7.2, C8.2, C9.2, C10.2, C11.2, C12.2, C13.2, C14.2, C15.2, C16.2, C17.2, C18.2, C19.2, C20.2, C21.2, C22.2, C26.2, C27.2, C28.2, C29.2, C32.2, C33.2, C34.2, C35.2, C36.2, C37.2, C38.2, C39.2, C40.2, C41.2, C50.2, C51.2, D2.1 (K), D5.2 (A), D8.2 (A), D9.2 (A), D10.1 (K), J1.2, J2.2, J3.2, Q4.1 (S), Q4.2 (S), Q4.3 (S), Q5.1 (S), Q5.2 (S), Q5.3 (S), R6.2, R8.2, R11.2, R20.2, R22.2, R23.2, R24.2, R42.2, R43.2, R52.2, R53.2, U1.11 (OV), U1.12 (GND), U2.10 (DTRK), U2.17 (AGND), U2.30 (PGND), U2.39 (EP), U3.8 (GND), U3.11 (MODE), U3.15 (PGTH), U3.25 (EP), U4.8 (GND), U4.11 (MODE), U4.15 (PGTH), U4.25 (EP)

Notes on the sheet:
PSU board - how this sheet works (docs/PSU_SPEC.md)
1. J1 takes the vehicle battery (16 AWG, 20 A fuse at the battery) or a bench supply, 6 to 36 V; it feeds both boards by their own cables from one ground.
2. D1 + D2 clamp the input at +111 V / -27 V. U1 LTC4364: Q1 clamps B0 at 48 V through a load dump (fault timer C2), Q2 blocks reverse current and back-feed.
3. B0 -> L3 -> L2 -> R2 -> VIN: a two-stage filter, damped by C17/C18 (Middlebrook); R2 is U2's input current limit (16.3 A).
4. U2 LM5177 four-switch buck-boost: 12.0 V from 2.9 to 60 V (BIAS from +12V once running), 400 kHz with spread spectrum.
5. U3 (2.0 A) feeds the adapter's J1001 through J2; U4 (3.0 A) feeds the KV260's J12 through J3. Both: OVP 14.4 V, UVLO 8.0 V.
6. R13-R16 (gate resistors) are 0 ohm: raise them to slow the switching edges if the EMI measurement asks for it.

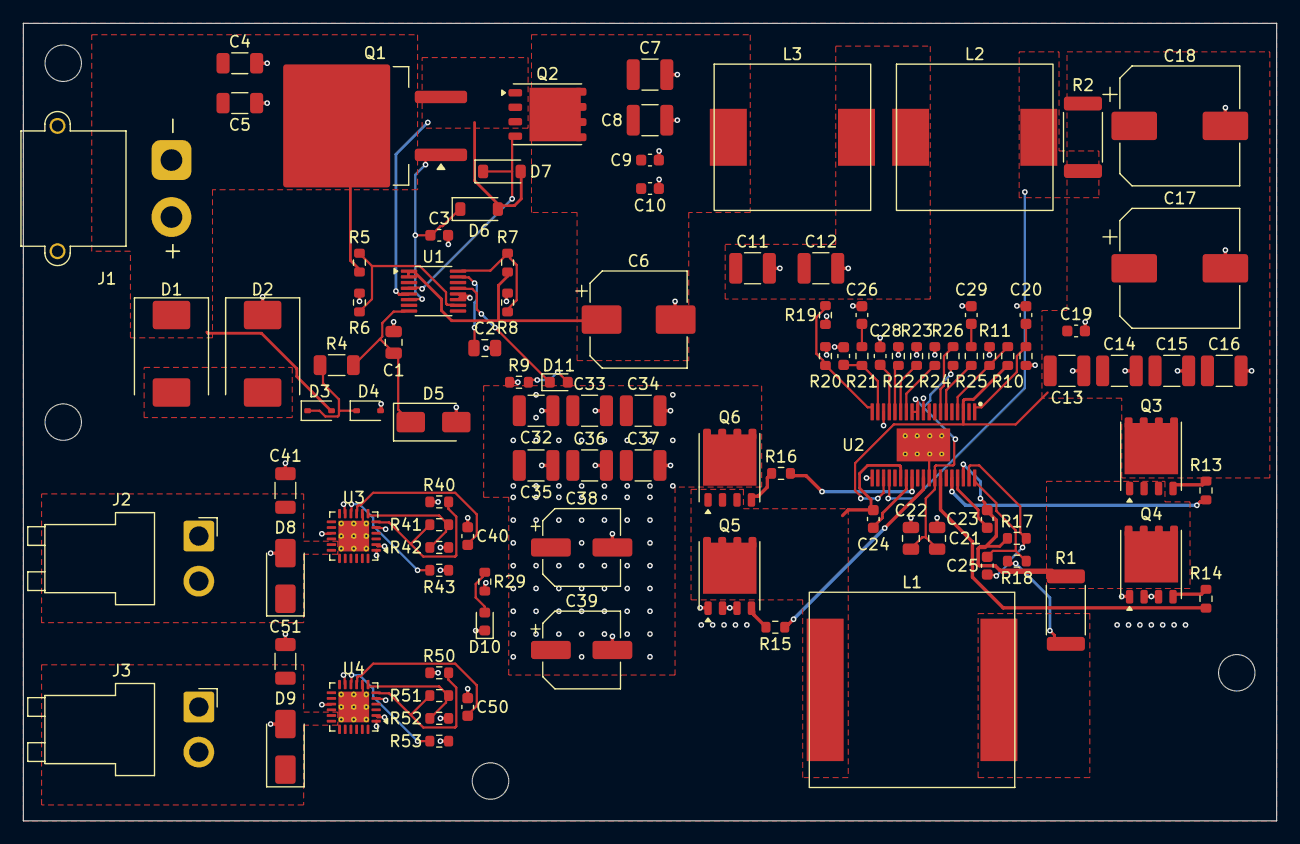
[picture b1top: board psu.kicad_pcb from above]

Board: 4 copper layers, 110.0 x 70.0 mm, 106 parts (0 on the bottom side), 57 nets.

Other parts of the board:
H1, H2, H3, H4: M3; MountingHole_3.2mm_M3

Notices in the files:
README.md:
Licence:
Licensed under the **Apache License 2.0**; see [`LICENSE`](LICENSE). Third-party MIT notices for the inherited Allied Vision CSI-2 adapter reference (`2023`) and verbatim `AERIS-10 / PLFM_RADAR` DSP modules (`fpga/third_party/aeris/`) are preserved in [`LICENSE`](LICENSE).
under the MIT licence (see [LICENSE](LICENSE)). What is kept from that design:
